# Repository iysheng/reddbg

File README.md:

### Debug TTL&232
设计了一款可以拼接的 USB 转 TTL/232 的模块

* [ ] 支持 USB 转 TTL
* [ ] 支持链接 TTL 转 232 扩展为 USB 转 232

#### 3D 效果图
正视图

俯视图

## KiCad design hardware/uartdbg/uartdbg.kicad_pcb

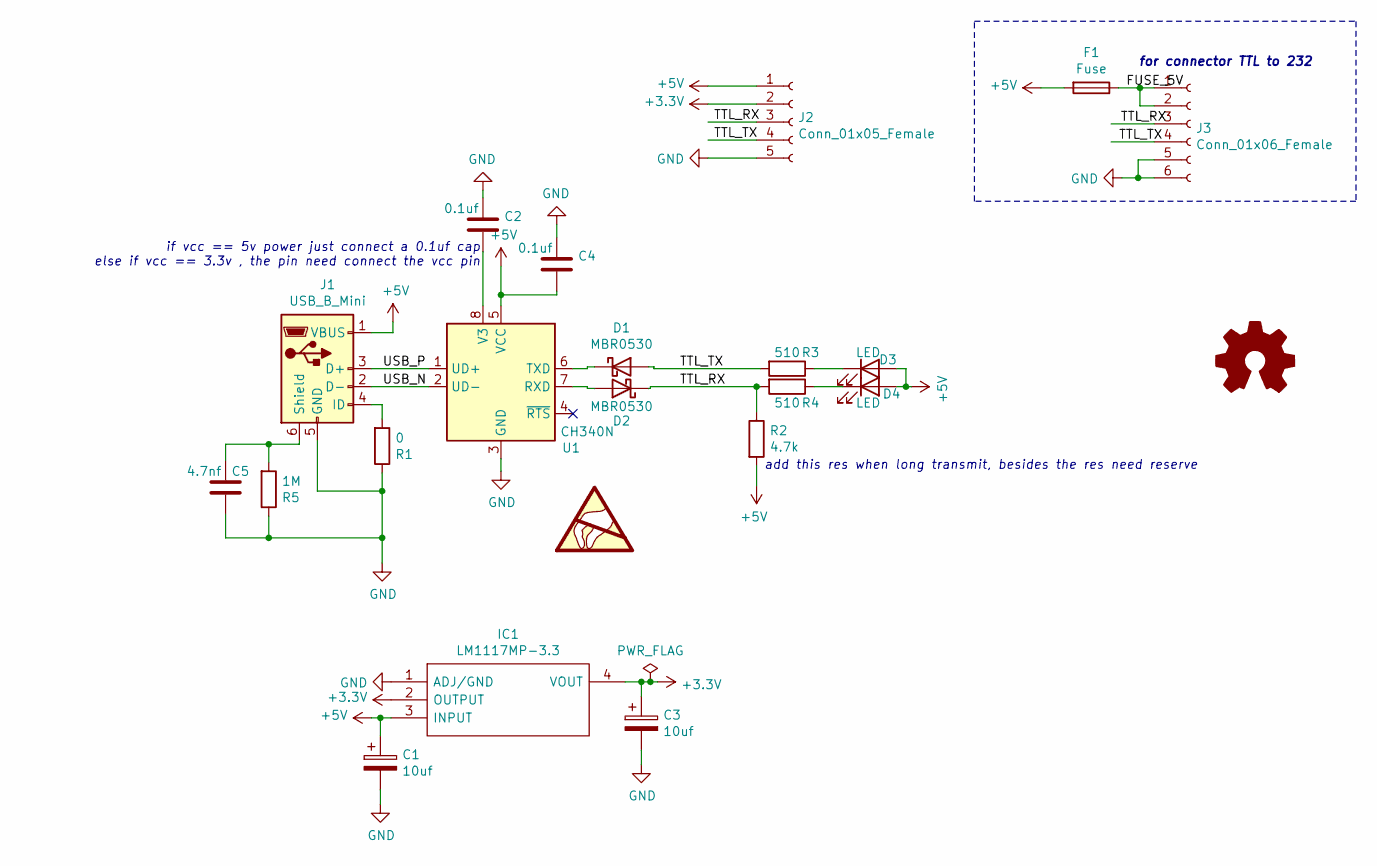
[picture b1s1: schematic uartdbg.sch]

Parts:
C1, C3: 10uf; CP_EIA-7343-31_Kemet-D_Pad2.25x2.55mm_HandSolder
C2, C4: 0.1uf; C_0603_1608Metric_Pad1.08x0.95mm_HandSolder
C5: 4.7nf; C_0603_1608Metric_Pad1.08x0.95mm_HandSolder
D1, D2: MBR0530; D_SOD-123
D3, D4: LED; LED_0603_1608Metric_Pad1.05x0.95mm_HandSolder
F1: Fuse; Fuse_1206_3216Metric_Pad1.42x1.75mm_HandSolder
IC1: LM1117MP-3.3; SOT230P700X180-4N; Manufacturer_Part_Number LM1117MP-3.3; Mouser Part Number 926-LM1117MP-33
J1: USB_B_Mini; USB_Mini-B_Lumberg_2486_01_Horizontal
J2: Conn_01x05_Female; PinHeader_1x05_P2.54mm_Vertical
J3: Conn_01x06_Female; TE_84952-6_1x06-1MP_P1.0mm_Horizontal
LOGO1: Logo_Open_Hardware_Small; OSHW-Logo2_7.3x6mm_Copper
R1: 0; R_0603_1608Metric_Pad0.98x0.95mm_HandSolder
R2: 4.7k; R_0603_1608Metric_Pad0.98x0.95mm_HandSolder
R3, R4: 510; R_0603_1608Metric_Pad0.98x0.95mm_HandSolder
R5: 1M; R_0603_1608Metric_Pad0.98x0.95mm_HandSolder
U1: CH340N; SOIC-8-CH340N

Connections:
+3V3: C3.1, IC1.2 (OUTPUT), IC1.4 (VOUT), J2.2
+5V: C1.1, C4.2, D3.2 (A), D4.2 (A), F1.2, IC1.3 (INPUT), J1.1 (VBUS), J2.1, R2.2, U1.5 (VCC)
/FUSE_5V: F1.1, J3.1, J3.2
/TTL_RX: D2.1 (K), J2.3, J3.3, R2.1, R4.2
/TTL_TX: D1.2 (A), J2.4, J3.4, R3.2
/USB_N: J1.2 (D-), U1.2 (UD-)
/USB_P: J1.3 (D+), U1.1 (UD+)
GND: C1.2, C2.1, C3.2, C4.1, C5.2, IC1.1 (ADJ/GND), J1.5 (GND), J2.5, J3.5, J3.6, R1.1, R5.1, U1.3 (GND)
unnamed: C2.2, U1.8 (V3)
unnamed: C5.1, J1.6 (Shield), R5.2
unnamed: D1.1 (K), U1.6 (TXD)
unnamed: D2.2 (A), U1.7 (RXD)
unnamed: D3.1 (K), R3.1
unnamed: D4.1 (K), R4.1
unnamed: J1.4 (ID), R1.2

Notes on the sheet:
if vcc == 5v power just connect a 0.1uf cap else if vcc == 3.3v , the pin need connect the vcc pin
add this res when long transmit, besides the res need reserve
for connector TTL to 232

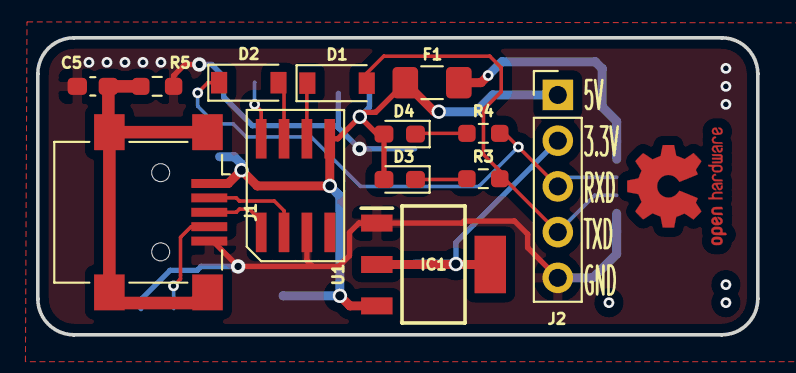
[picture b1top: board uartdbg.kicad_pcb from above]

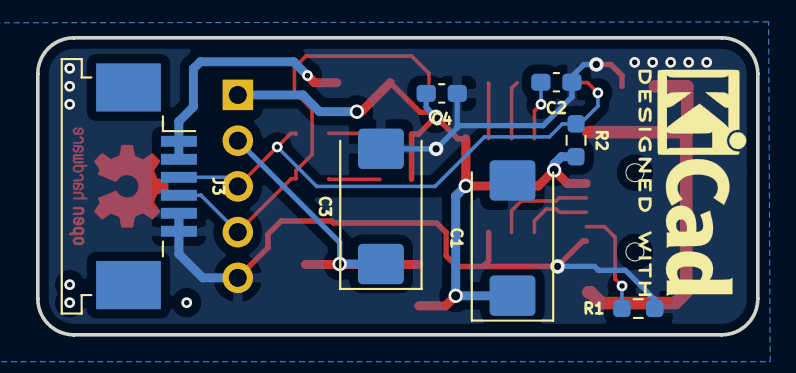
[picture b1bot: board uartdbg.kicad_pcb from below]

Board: 2 copper layers, 40.0 x 16.5 mm, 22 parts (8 on the bottom side), 15 nets.

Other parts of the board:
REF_1: KiCad-Logo2_5mm_SilkScreen

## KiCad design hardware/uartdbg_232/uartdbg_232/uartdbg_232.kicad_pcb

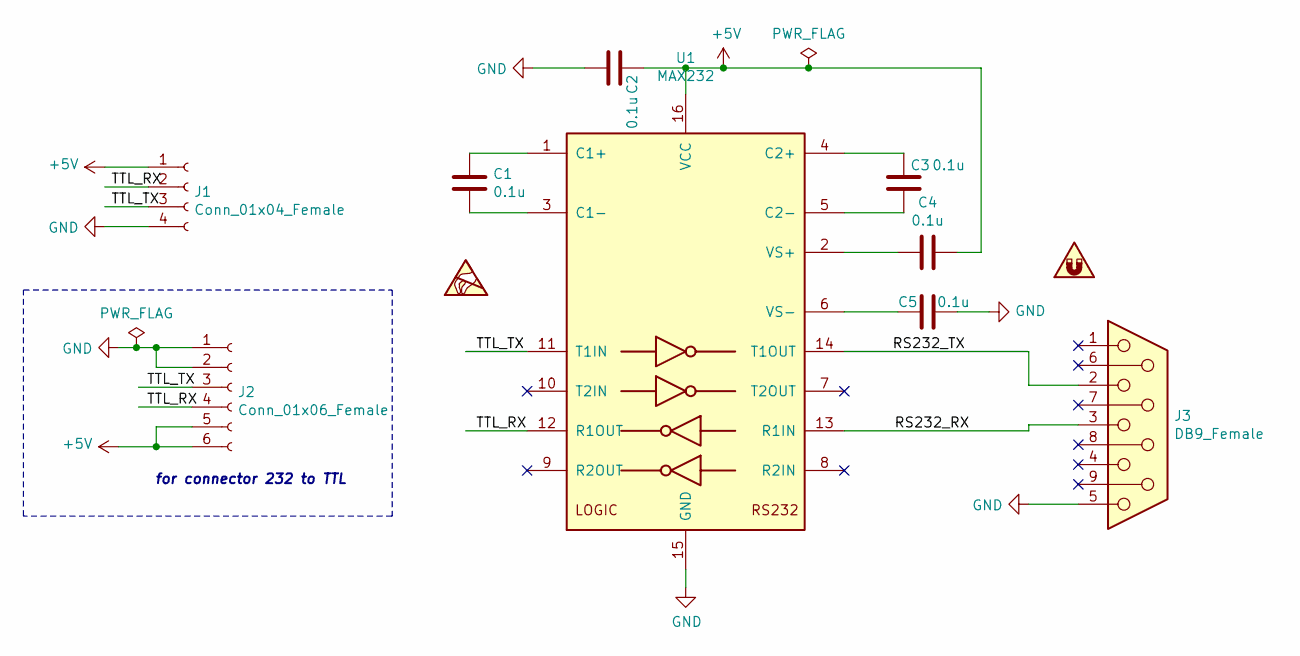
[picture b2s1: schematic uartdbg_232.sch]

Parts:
C1, C2, C3, C4, C5: 0.1u; C_0603_1608Metric_Pad1.08x0.95mm_HandSolder
J1: Conn_01x04_Female; PinHeader_1x04_P2.54mm_Vertical
J2: Conn_01x06_Female; TE_84952-6_1x06-1MP_P1.0mm_Horizontal
J3: DB9_Female; DSUB-9_Female_Horizontal_P2.77x2.84mm_EdgePinOffset7.70mm_H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
SYM1: SYM_ESD_Small; ESD-Logo_6.6x6mm_SilkScreen
SYM2: SYM_Magnet_Small; OSHW-Logo2_7.3x6mm_Copper
U1: MAX232; SOIC127P1032X265-16N

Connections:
+5V: C2.1, C4.1, J1.1, J2.5, J2.6, U1.16 (VCC)
/RS232_RX: J3.3, U1.13 (R1IN)
/RS232_TX: J3.2, U1.14 (T1OUT)
/TTL_RX: J1.2, J2.4, U1.12 (R1OUT)
/TTL_TX: J1.3, J2.3, U1.11 (T1IN)
GND: C2.2, C5.1, J1.4, J2.1, J2.2, J3.5, U1.15 (GND)
unnamed: C1.1, U1.1 (C1+)
unnamed: C1.2, U1.3 (C1-)
unnamed: C3.1, U1.4 (C2+)
unnamed: C3.2, U1.5 (C2-)
unnamed: C4.2, U1.2 (VS+)
unnamed: C5.2, U1.6 (VS-)

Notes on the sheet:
for connector 232 to TTL

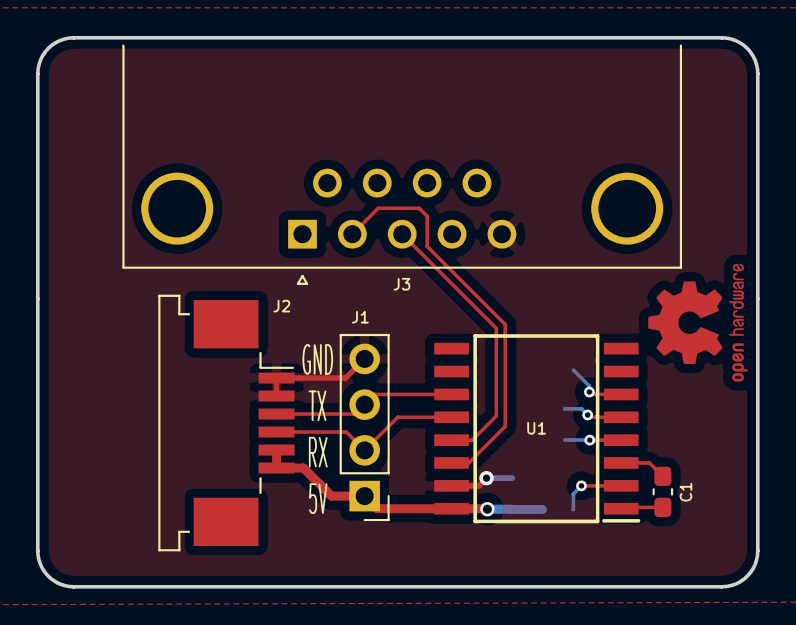
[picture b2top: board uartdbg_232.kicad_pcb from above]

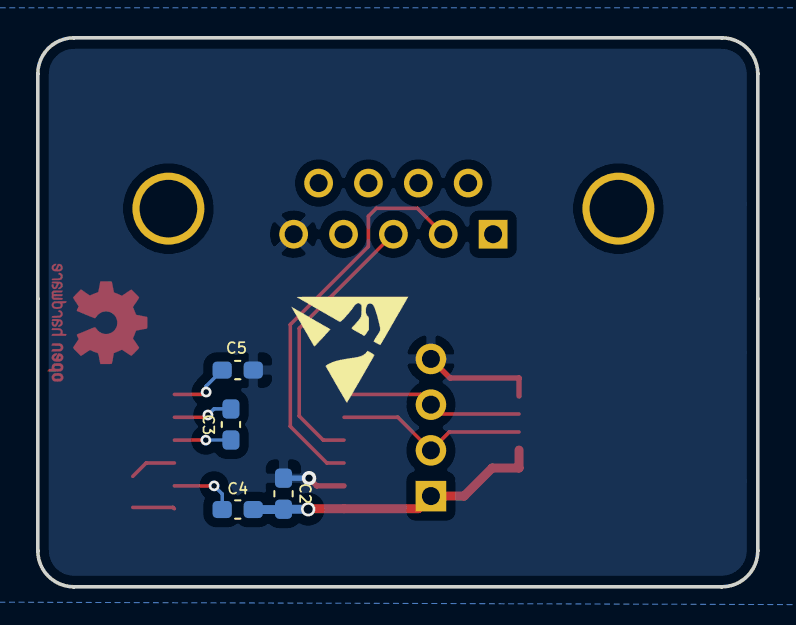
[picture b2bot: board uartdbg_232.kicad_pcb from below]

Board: 2 copper layers, 40.0 x 30.5 mm, 11 parts (5 on the bottom side), 12 nets.

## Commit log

2021-06-07 [ADD][N/A] 添加设计文档和芯片手册
2021-06-07 [ADD][N/A] 添加 README 文档
2021-06-07 [ADD][N/A] 添加硬件设计文档
2021-06-07 [ADD][CHG][NT] 更新原理图和 3D 封装库等内容
2021-06-08 [CHG][ADD][NT] 更新原理图和 PCB,添加额外的保护以及 logo,添加 geber 文件包
2021-06-08 [CHG][N/A] 修改 README 的描述,展示 3D 效果图
2021-06-08 [CHG][N/A] 更新 README 功能描述
2021-06-11 [CHG][NT] 更新原理图和 PCB 对 TX 和 RX LED 灯具状态指示管脚接线为上拉
2021-06-15 [ADD][CHG][NT] 1. 添加 232 的原理图和 pcb 布局 2. 添加 232 的边框文件
2021-08-01 [CHG][NT] 暂存
